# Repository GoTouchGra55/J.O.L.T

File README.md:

# 🚧 Under Active Development 🚧

# J.O.L.T ⚡

## Overview

JOLT (short for Joint Operated Legged Terrain walker) is my attempt at making a 12-DOF quadruped robot from scratch.

Yes, I designed a custom STM32-based dev board, CAD, and will implement custom firmware! :3

---

### PCB Design (2-layer)

#### Routing

### Schematics

### Mechanical Design

Btw you might be wondering why there are so many triangular cutouts in the design.
Well first of all, it looks cool and secondly, I read an article about why triangles = **strong**.
I won't bother explaining the physics here but, you can do your own research on why that is.

*For those interested in the engineering principles, you can read more about why this geometry is superior for weight-to-strength ratios here: 
https://www.youtube.com/watch?v=Hn_iozUo9m4*

.stl files can be found at 

---

## System Architecture

### Power System

2s LiPo input (7.4V nominal voltage) is regulated to 5V and 3.3V rails for logic and peripherals.

Definitely don't use a higher cell lipo (unless you want to witness the magic smoke :p).

### Control System

An STM32F405RGT6 MCU handles the math and motion control while a PCA9685 PWM servo controller chip controls all 12 servos across 4 legs.

### Sensing

An onboard IMU provides orientation and motion feedback.

---

## Hardware

### Actuators

| Joint     | Servo  | Count |
| --------- | ------ | ----- |
| Hip yaw   | MG996R | 4     |
| Hip pitch | MG996R | 4     |
| Knee      | MG996R | 4     |

---

### Development Board

| Component    | Part            |
| ------------ | --------------- |
| MCU          | STM32F405RGT6   |
| IMU          | ICM42688-P      |
| Servo Driver | PCA9685BS       |
| Power        | 5V + 3.3V LDO   |
| Debug        | ST-Link v2      |
| Input        | XT-60 (2s LiPo) |

## Assembly Guide

### Electronics

Unless you want a _not so pleasant_ experience, I'd advise you to follow the order below:

1. Solder all SMD components first (MCU, IMU, passives)
2. Solder larger components (connectors, headers)
3. Verify power rails (5V, 3.3V) before powering MCU
4. Flash firmware via ST-Link
5. Connect servos and test individual joints

### Body

1. Check parts for any sign of damage. Damaged part = Sad quadruped :(
2. Insert each servo into its respective slot and screw with suitable screws.
3. Make wiring as untangled as possible (because everyone likes cable management, right?)

---

## ⚠️ Warning

1. Double-check polarity of capacitors and power input before powering the board. Otherwise you've made a fancy capacitor bomb :D
2. Use a 2s LiPo battery to ensure safety of components
3. **DO NOT** expose the LiPo battery to high heat or poke the cells.

---

## Firmware

In progress...

---

## Project Status

- [x] CAD
- [x] PCB
- [ ] Assembly
- [ ] Initial tests

---

## Bill of Materials

| Name | Purpose | Quantity | Total Cost (USD) | Distributor |
|------|---------|---------:|-----------------:|------------|
| Brass inserts | To secure the screws | 1 | 4.21 | Daraz Nepal |
| Metal Servo Horns | To connect servo with the linkages | 2 | 18.35 | Daraz Nepal |
| Bearings | To ensure smooth movement | 1 | 5.47 | Daraz Nepal |
| 0603 Resistors | Used in circuit | 1 | 4.58 | Daraz Nepal |
| Devboard PCB | The brains and the body of the quadruped | 1 | 135.41 | JLCPCB |
| Female Header Pins | For GPIO pins | 1 | 0.71 | Daraz Nepal |
| XT-60 Connector | To connect the battery to the board | 1 | 0.54 | Daraz Nepal |
| M4 Screws | To secure the components | 1 | 3.96 | Daraz Nepal |
| MG996R Servos | To move the joints of the robot | 12 | 41.08 | Daraz Nepal |
| Capacitor | Used in circuit | 1 | 0.65 | Daraz Nepal |
| Tweezers | To hold tiny 0201 components | 1 | 2.62 | Daraz Nepal |
| Solder Paste | For soldering | 1 | 4.26 | Daraz Nepal |
| Shipping | Shipping costs | 1 | 26.81 | Daraz Nepal + JLCPCB |
| **Total** |  |  | **248.65** |  |

---

## License

MIT License - see [LICENSE](LICENSE)

---

## Author

**Shaurya Tamang**  
GitHub: https://github.com/GoTouchGra55  
Website: https://shauryatamang.netlify.app

---

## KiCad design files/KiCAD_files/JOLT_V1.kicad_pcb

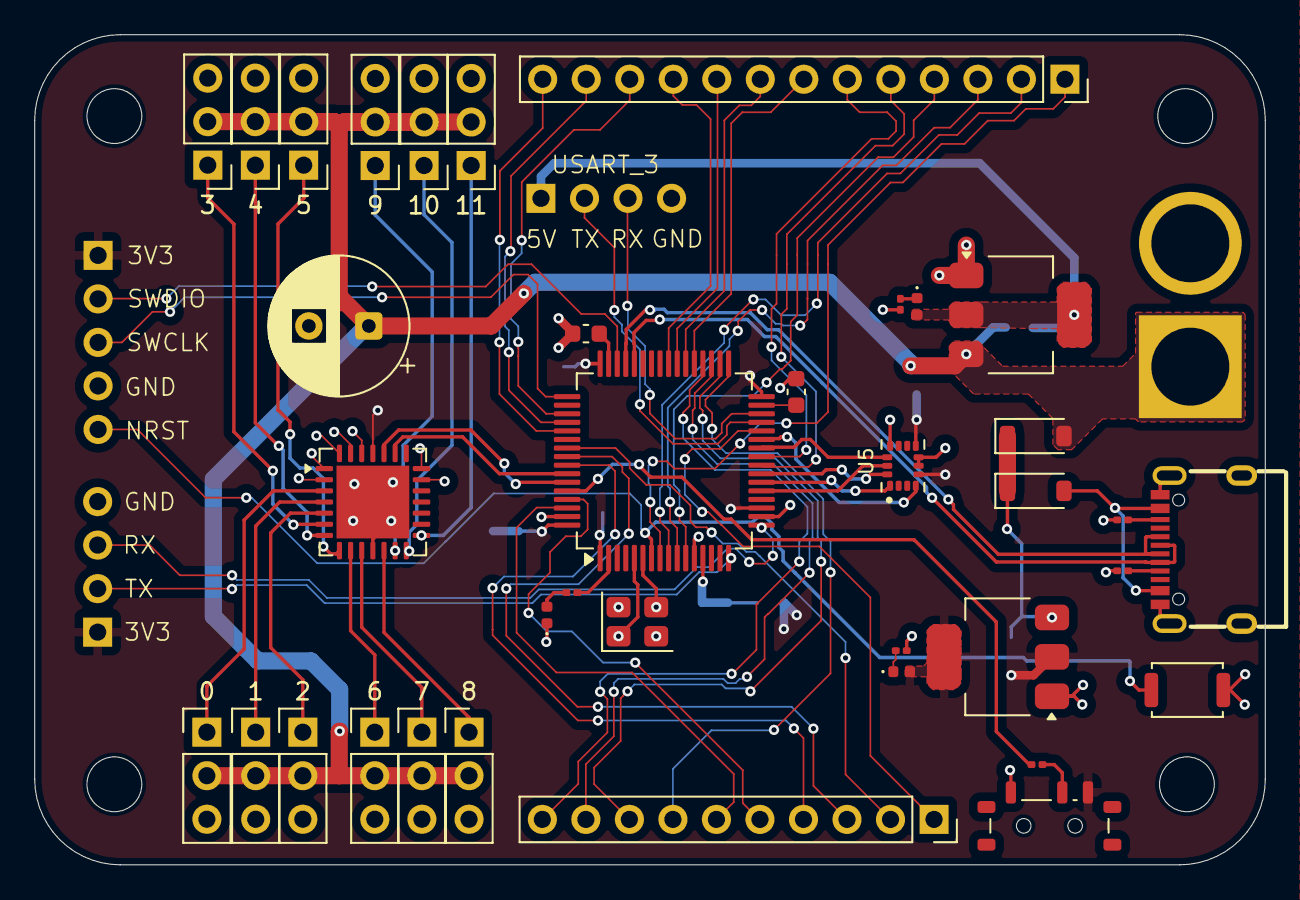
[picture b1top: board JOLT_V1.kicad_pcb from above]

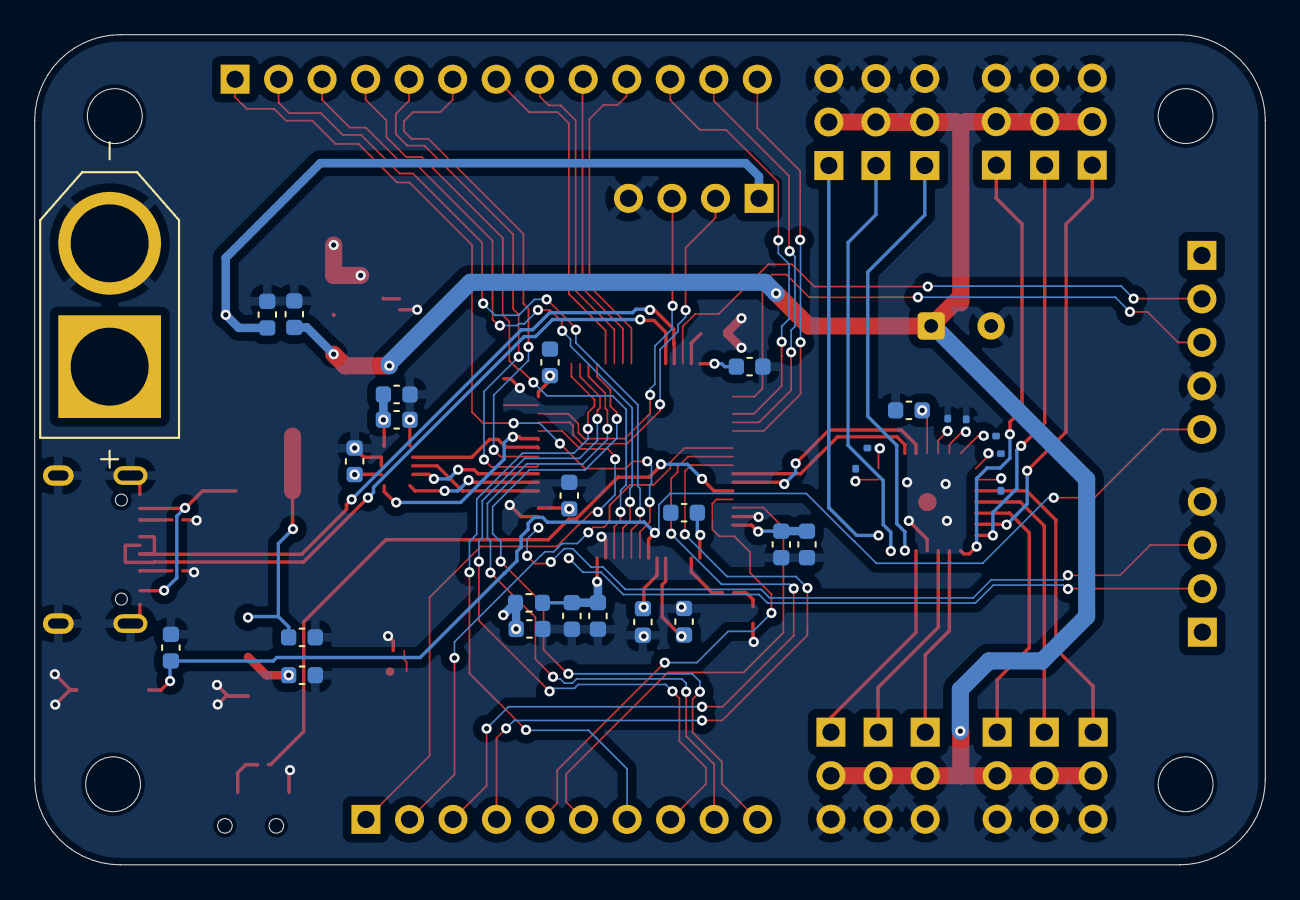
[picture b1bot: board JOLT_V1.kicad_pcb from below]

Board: 2 copper layers, 71.8 x 48.5 mm, 73 parts (29 on the bottom side), 77 nets.

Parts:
0, 1, 2, 3, 4, 5, 6, 7, 8, 9, 10, 11: Conn_01x03_Pin; PinHeader_1x03_P2.54mm_Vertical
C1, C2, C3, C4, C5, C7, C10, C11: 100nF; C_0603_1608Metric
C6: 10uF; C_0603_1608Metric
C8, C9: 1uF; C_0603_1608Metric
C12, C13, C22, C23: 22uF; C_0603_1608Metric
C14: 2200uF; CP_Radial_D8.0mm_P3.50mm
C15, C16: 10pF; C_0603_1608Metric
C17, C18, C20: 2.2uF; C_0603_1608Metric
C19: 0.1uF; C_0603_1608Metric
C21: 10nF; C_0603_1608Metric
D1: LED; LED_0402_1005Metric
D2, D3: RED; LED_0402_1005Metric
D4, D5: SS14; D_SOD-123
FB1: 120R; L_0603_1608Metric
H1, H2, H3, H4: MountingHole_3.2mm_M3
J1, J3: Conn_01x04_Pin; PinHeader_1x04_P2.54mm_Vertical
J2: Conn_01x10_Socket; PinSocket_1x10_P2.54mm_Vertical
J4: XT60-M; AMASS_XT60-M
J5: Conn_01x13_Socket; PinSocket_1x13_P2.54mm_Vertical
J13: Conn_01x05_Pin; PinHeader_1x05_P2.54mm_Vertical
R1, R12, R13, R14, R15, R16, R17, R18: 10k; R_0201_0603Metric
R2, R3: 1K; R_0201_0603Metric
R9: 330; R_0201_0603Metric
R10, R11: 5.1k; R_0201_0603Metric
SW1: SW_Push; SW_Push_SPST_NO_Alps_SKRK
SW2: SW_SPDT; SW_SPDT_Shouhan_MSK12C02
U1: STM32F405RGT6; LQFP-64_10x10mm_P0.5mm
U2: AMS1117-3.3; SOT-223-3_TabPin2
U3: PCA9685BS; QFN-28-1EP_6x6mm_P0.65mm_EP4.25x4.25mm
U4: AMS1117-5.0; SOT-223-3_TabPin2
U5: ICM-42688-P; PQFN50P300X250X97-14N
USB1: TYPE-C 16PIN 2MD(073); USB-C-SMD_TYPE-C-6PIN-2MD-073
Y1: 16MHz; Crystal_SMD_3225-4Pin_3.2x2.5mm

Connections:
+3.3V: C1.1, C2.1, C3.1, C4.1, C5.1, C6.1, C9.1, C11.1, C13.1, C19.1, C20.1, C21.1, D2.2 (A), FB1.2, J1.1, J13.1, SW2.3 (C), U1.1 (VBAT), U1.19 (VDD), U1.32 (VDD), U1.48 (VDD), U1.64 (VDD), U2.2 (VO), U3.25 (VDD), U5.5 (VDDIO), U5.8 (VDD)
+3.3VA: C7.1, C8.1, FB1.1, U1.13 (VDDA)
+5V: C23.1, D3.2 (A), J3.1, U4.2 (VO)
/Main/GPIO0: J2.1, U1.28 (PB2)
/Main/GPIO1: J2.2, U1.55 (PB3)
/Main/GPIO2: J2.3, U1.56 (PB4)
/Main/GPIO3: J2.4, U1.57 (PB5)
/Main/GPIO4: J2.5, U1.61 (PB8)
/Main/GPIO5: J2.6, U1.62 (PB9)
/Main/GPIO6: J2.7, U1.33 (PB12)
/Main/GPIO7: J2.8, U1.34 (PB13)
/Main/GPIO8: J2.9, U1.35 (PB14)
/Main/GPIO9: J2.10, U1.36 (PB15)
/Main/GPIO10: J5.1, U1.8 (PC0)
/Main/GPIO11: J5.2, U1.9 (PC1)
/Main/GPIO12: J5.3, U1.10 (PC2)
/Main/GPIO13: J5.4, U1.11 (PC3)
/Main/GPIO14: J5.5, U1.24 (PC4)
/Main/GPIO15: J5.6, U1.25 (PC5)
/Main/GPIO16: J5.7, U1.37 (PC6)
/Main/GPIO17: J5.8, U1.38 (PC7)
/Main/GPIO18: J5.9, U1.39 (PC8)
/Main/GPIO19: J5.10, U1.40 (PC9)
/Main/GPIO20: J5.11, U1.51 (PC10)
/Main/GPIO21: J5.12, U1.52 (PC11)
/Main/GPIO22: J5.13, U1.53 (PC12)
/Main/HSE_IN: C15.1, U1.5 (PH0), Y1.1
/Main/HSE_OUT: C16.1, U1.6 (PH1), Y1.3
/Main/NRST: C10.2, J13.5, SW1.2, U1.7 (NRST)
/Main/SWCLK: J13.3, U1.49 (PA14)
/Main/SWDIO: J13.2, U1.46 (PA13)
/Main/USART2_RX: J1.3, U1.17 (PA3)
/Main/USART2_TX: J1.2, U1.16 (PA2)
/Main/USB_DN: U1.44 (PA11), USB1.5 (DN2), USB1.7 (DN1)
/Main/USB_DP: U1.45 (PA12), USB1.6 (DP1), USB1.8 (DP2)
/Servo_Controller/SERVO_0: 0.1, U3.3 (LED0)
/Servo_Controller/SERVO_1: 1.1, U3.4 (LED1)
/Servo_Controller/SERVO_2: 2.1, U3.5 (LED2)
/Servo_Controller/SERVO_3: 3.1, U3.6 (LED3)
/Servo_Controller/SERVO_4: 4.1, U3.7 (LED4)
/Servo_Controller/SERVO_5: 5.1, U3.8 (LED5)
/Servo_Controller/SERVO_6: 6.1, U3.9 (LED6)
/Servo_Controller/SERVO_7: 7.1, U3.10 (LED7)
/Servo_Controller/SERVO_8: 8.1, U3.12 (LED8)
/Servo_Controller/SERVO_9: 9.1, U3.13 (LED9)
/Servo_Controller/SERVO_10: 10.1, U3.14 (LED10)
/Servo_Controller/SERVO_11: 11.1, U3.15 (LED11)
GND: 0.3, 1.3, 2.3, 3.3, 4.3, 5.3, 6.3, 7.3, 8.3, 9.3, 10.3, 11.3, C1.2, C2.2, C3.2, C4.2, C5.2, C6.2, C7.2, C8.2, C9.2, C10.1, C11.2, C12.2, C13.2, C14.2, C15.2, C16.2, C17.1, C18.1, C19.2, C20.2, C21.2, C22.2, C23.2, D1.1 (K), J1.4, J3.4, J4.N (NEG), J13.4, R2.2, R3.2, R10.1, R11.1, R12.2, R13.2, R14.2, R15.2, R16.2, R17.2, R18.2, SW1.1, SW2.1 (A), U1.12 (VSSA), U1.18 (VSS), U1.63 (VSS), U2.1 (GND), U3.11 (VSS), U3.29 (VSS), U4.1 (GND), U5.6 (GND), U5.7 (RESV_7), U5.11 (RESV_11), USB1.1 (GND), USB1.12 (GND), USB1.13 (SHELL), USB1.14 (SHELL), Y1.2 (G), Y1.4 (G)
I2C_SCL: U1.58 (PB6), U3.23 (SCL)
I2C_SDA: U1.59 (PB7), U3.24 (SDA)
IMU_CS: U1.26 (PB0), U5.12 (AP_CS)
IMU_INT1: U1.27 (PB1), U5.4 (INT1/INT)
unnamed: D1.2 (A), R9.1
unnamed: D2.1 (K), R2.1
unnamed: D3.1 (K), R3.1
unnamed: C12.1, D4.1 (K), D5.1 (K), U2.3 (VI)
unnamed: R1.1, SW2.2 (B)
unnamed: R1.2, U1.60 (BOOT0)
unnamed: R9.2, U1.2 (PC13)
unnamed: C17.2, U1.31 (VCAP_1)
unnamed: C18.2, U1.47 (VCAP_2)
unnamed: R13.1, U3.26 (A0)
unnamed: R14.1, U3.27 (A1)
unnamed: R15.1, U3.28 (A2)
unnamed: R16.1, U3.1 (A3)
unnamed: R17.1, U3.2 (A4)
unnamed: R18.1, U3.21 (A5)
unnamed: R12.1, U3.20 (~OE)
unnamed: R11.2, USB1.4 (CC1)
unnamed: R10.2, USB1.10 (CC2)
SERVO_PWR: 0.2, 1.2, 2.2, 3.2, 4.2, 5.2, 6.2, 7.2, 8.2, 9.2, 10.2, 11.2, C14.1, C22.1, D5.2 (A), J4.P (POS), U4.3 (VI)
SPI_MISO: U1.22 (PA6), U5.1 (AP_SDO/AP_AD0)
SPI_MOSI: U1.23 (PA7), U5.14 (AP_SDA/AP_SDIO/AP_SDI)
SPI_SCK: U1.21 (PA5), U5.13 (AP_SCL/AP_SCLK)
USART3_RX: J3.3, U1.30 (PB11)
USART3_TX: J3.2, U1.29 (PB10)
VBUS: D4.2 (A), USB1.2 (VBUS), USB1.11 (VBUS)

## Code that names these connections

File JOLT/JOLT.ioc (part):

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Mcu.Name=STM32F405RGTx
Mcu.Package=LQFP64
Mcu.UserName=STM32F405RGTx
PA11.Mode=Device_Only
PA11.Signal=USB_OTG_FS_DM
PA12.Mode=Device_Only
PA12.Signal=USB_OTG_FS_DP
PA13.Mode=Serial_Wire
PA13.Signal=SYS_JTMS-SWDIO
PA14.Mode=Serial_Wire
PA14.Signal=SYS_JTCK-SWCLK
PA2.Mode=Asynchronous
PA2.Signal=USART2_TX
PA3.Mode=Asynchronous
PA3.Signal=USART2_RX
PA5.Mode=Full_Duplex_Master
PA5.Signal=SPI1_SCK
PA6.Mode=Full_Duplex_Master
PA6.Signal=SPI1_MISO
PA7.Mode=Full_Duplex_Master
PA7.Signal=SPI1_MOSI
PB0.Signal=GPIO_Output
PB1.Signal=GPIO_Input
PB10.Mode=Asynchronous
PB10.Signal=USART3_TX
PB11.Mode=Asynchronous
PB11.Signal=USART3_RX
PB2.Signal=GPIO_Input
PB6.Mode=I2C
PB6.Signal=I2C1_SCL
PB7.Mode=I2C
PB7.Signal=I2C1_SDA
PC13-ANTI_TAMP.GPIOParameters=GPIO_Label
PC13-ANTI_TAMP.GPIO_Label=STATUS_LED
PC13-ANTI_TAMP.Signal=GPIO_Output
PH0-OSC_IN.Mode=HSE-External-Oscillator
PH0-OSC_IN.Signal=RCC_OSC_IN
PH1-OSC_OUT.Mode=HSE-External-Oscillator
PH1-OSC_OUT.Signal=RCC_OSC_OUT
RCC.HSE_VALUE=25000000
RCC.SYSCLKFreq_VALUE=168000000
RCC.SYSCLKSource=RCC_SYSCLKSOURCE_PLLCLK
board=custom

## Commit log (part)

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2026-03-21 Add files and README.md
2026-03-23 Add STEP files and update README.md
2026-03-24 Mark Hip bracket CAD as completed
2026-03-24 Add 3d files
2026-03-25 Modify CAD project status in README
    Updated the status of the Body plate and added Chassis finalization.
2026-04-04 Add project files
2026-04-04 Add checks
2026-04-05 Add modified files
2026-04-05 Add final files
2026-04-06 Add BOM
2026-04-18 Add new files after review and update readme
2026-04-20 Update files
2026-04-23 Update README and add updated files for printing
2026-04-23 Enhance README with design rationale
    Added explanation for triangular cutouts in design.
2026-04-23 Add error-fixed files
2026-04-26 Add badges to README
2026-04-26 Add link to engineering principles in README
    Added a reference link for engineering principles related to design geometry.
2026-04-27 Add 4 layer pcb and update readme
2026-05-06 Update to 2-layer pcb
2026-05-06 Add updated kicad files
2026-05-25 Update files for Forge
2026-05-25 Update Journal
2026-06-01 Update files #2
2026-06-01 Update #3
2026-06-01 Update #4
2026-06-01 Update #5
2026-06-01 Update #6
2026-06-02 Update Bill of Materials with cost adjustments
2026-06-08 Refine component descriptions in README
    Updated descriptions for Tweezers and Helping Hand with Magnifier to specify 0201 components.
2026-06-24 Update Bill of Materials with new items and costs
